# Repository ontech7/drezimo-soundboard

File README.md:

<h1>
  <picture>
    <source media="(prefers-color-scheme: dark)" srcset="assets/logo/drezimo-logo-dark.svg">
    
  </picture>
</h1>

A physical soundboard for [Voicemod](https://www.voicemod.net/): 36 pads, 6 function keys, a rotary encoder and a small OLED display, connected to the PC with a single USB cable.

**Status:** the first unit is built and works: the PCB (v0.2) with its keys, LEDs, display and knob, closed in its 3D-printed enclosure. The desktop app runs on Windows and macOS (Apple Silicon), comes with an installer for each and keeps itself and the board's firmware up to date.

## Hardware

- RP2040-Zero (RP2040, USB-C)
- 6×6 sound pads + 6 function keys, MX switches soldered to the PCB, 7×6 diode matrix
- 42 SK6812MINI-E reverse-mount RGB LEDs, one per key
- 1.3" SH1106 OLED (I²C) and an EC11 encoder with push button
- Custom 2-layer PCB
- 3D-printed enclosure in two parts, a top shell and a bottom, closed by six M3 screws from below
- Powered from USB only

<p align="center">
  
  <br>
  <sub>The bottom of the PCB v0.2 as the fab assembles it: the LEDs and the small parts. The switches, the RP2040-Zero, the LED buffer, the knob and the display are soldered by hand.</sub>
</p>

<table>
  <tr>
    <td width="50%"></td>
    <td width="50%"></td>
  </tr>
  <tr>
    <td align="center"><sub>The top shell: the logo and the function keys' labels are printed flush in white</sub></td>
    <td align="center"><sub>The bottom, from inside: six standoffs for the screws, ribs and posts under the keys, keyholes for an optional stand</sub></td>
  </tr>
</table>

## The app

- **Soundboard:** the board's current page in the window, with Voicemod's pictures and the LEDs' live colours, playable from there too, and the display's live picture. Voicemod's soundboards and voices come as pages of 36 pads; a sound outside the Voicemod licence blinks red with "PRO ONLY" when pressed.
- **Your own pages:** sounds, voices and actions (stop the sounds, mute the microphone, the voice changer, a random voice, hear myself, mute for me, background effects, go to a page, the overlay, the volumes back) in the order you want, with your own names, LED colours and sound volumes, before Voicemod's soundboards on the board.
- **Macros:** one pad playing sounds on tracks along a time line, one after the other or over each other, cut where you want and with their own volume, with voices and switches at their times; How it works walks through the editor with a time line to try.
- **PC overlay:** the page's sounds on top of the other windows when the page changes or the knob is held, on the screen and in the corner you choose.
- **Action wheel:** if you want it, a knob gesture opens a wheel of your shortcuts on the screen, pages, actions or macros around the Drezimo logo, and turning the knob picks one.
- **Updates:** the app updates itself and the board's firmware, and says what is new.
- **Support:** a report to copy, without personal paths, and a hardware test for a board just built.
- In English and Italian.

<p align="center">
  
  <br>
  <sub>The Macro editor: sounds on tracks along a time line, the music fading in and out under the others, voices and switches at their times</sub>
</p>

<table>
  <tr>
    <td width="56%"></td>
    <td width="44%"></td>
  </tr>
  <tr>
    <td align="center"><sub>The page editor</sub></td>
    <td align="center"><sub>The action wheel, picked by turning the knob</sub></td>
  </tr>
</table>

<p align="center">
  
  <br>
  <sub>The PC overlay</sub>
</p>

## Installing the app

Download the Windows installer (`-setup.exe`) from [Releases](https://github.com/ontech7/drezimo-soundboard/releases). It needs Voicemod, free or PRO, on the same PC. The app then starts with Windows, in the notification area, and keeps itself and the board's firmware up to date. The installer is not code-signed: at the first install Windows asks to confirm an unknown publisher (More info → Run anyway).

On a Mac with Apple Silicon, download the disk image (`.dmg`), open it and drag Drezimo Soundboard to Applications. It also needs Voicemod, and keeps itself and the board's firmware up to date; starting with macOS is a switch in its Settings. The app is not signed by Apple: the first time, macOS refuses to open it, then System Settings → Privacy & Security → Open Anyway lets it start (or run `xattr -cr "/Applications/Drezimo Soundboard.app"`).

## How it works

The board talks to a desktop bridge app over USB. The app controls Voicemod through its Control API and reads Voicemod's log to know which sounds are actually playing, so the LEDs and the display match Voicemod's own soundboard. The app draws the display's pictures and the board shows them, so the texts are translated in the app.

## Repository layout

| Path | Contents |
|---|---|
| `hardware/scripts/` | Python scripts that generate the KiCad schematic and PCB, check the design and export review documents and fab files |
| `hardware/pcb/` | KiCad 10 project, generated by the scripts |
| `firmware/` | RP2040-Zero firmware (Arduino core for RP2040, built with `arduino-cli`) |
| `app/` | Bridge app for macOS and Windows (Tauri 2: Rust core, React settings window) |
| `site/` | Landing page with the board in 3D (three.js, Vite) and the latest installer; a Dockerfile serves it with nginx |
| `hardware/lib/` | Project symbol and footprints (RP2040-Zero, MX switch, logo silkscreen) |
| `hardware/enclosure/` | The 3D-printed enclosure, generated from the PCB file and caliper readings (Python, build123d): the generator, its tests and the print files |
| `assets/logo/` | Logo (SVG) and app icon |
| `simulator/dummy-board.html` | 1:1 browser simulator of the board; can connect to Voicemod |
| `tools/` | Voicemod API probe, log watcher and behaviour experiments |
| `docs/` | Design notes and decisions (`project.md`), screenshots |

## Building the hardware files

Requires KiCad 10. On macOS:

```sh
cd hardware/scripts
python3 build_schematic.py
python3 check_design.py
/Applications/KiCad/KiCad.app/Contents/Frameworks/Python.framework/Versions/Current/bin/python3 build_pcb.py
python3 export_docs.py   # schematic PDF, 1:1 fit-check PDFs, 3D renders, DRC report in hardware/docs/
/Applications/KiCad/KiCad.app/Contents/Frameworks/Python.framework/Versions/Current/bin/python3 export_fab.py
```

`build_pcb.py` and `export_fab.py` need KiCad's bundled Python, which provides the `pcbnew` module. Edit the scripts, not the generated KiCad files.

`export_fab.py` writes the JLCPCB package to `hardware/fab/`: the Gerber + drill zip, the assembly BOM with LCSC part numbers and the placement file (CPL). All assembled parts are on the bottom side; the SK6812MINI-E is a JLCPCB "Standard PCBA only" part. The switches, the RP2040-Zero, the SN74AHCT125N, the OLED module and the encoder are hand-soldered.

## Building the enclosure files

Requires [`uv`](https://docs.astral.sh/uv/), which installs Python and build123d on the first run.

```sh
cd hardware/enclosure
uv run python -m drezimo_case shell    # the top shell
uv run python -m drezimo_case bottom   # the bottom
uv run pytest -q
```

Each command writes the part to `hardware/enclosure/print/` as STEP and 3MF, lying as it is printed, with a picture of it cut through. With `--bambu` after the name, and Bambu Studio installed (macOS), it also writes a Bambu Studio project for the P1S with the print settings decided, sliced once as a check. The parts are drawn from the PCB file and from the caliper readings in `drezimo_case/measurements.py`; `docs/project.md` (section 7) says how.

## Building the firmware

Requires [`arduino-cli`](https://arduino.github.io/arduino-cli/) (`brew install arduino-cli` on macOS). The core and library versions are pinned in `firmware/drezimo/sketch.yaml` and downloaded on the first build.

```sh
./firmware/upload.sh          # build, then upload to the connected board
./firmware/build.sh --bundle  # build, then put the firmware into the app
```

The script works with the firmware running (it sends `BOOT` to reach the bootloader) or with the board already in bootloader mode: a blank module, or one plugged in while holding BOOT. It uploads with `picotool`; on macOS, copying the `.uf2` onto the RPI-RP2 drive can hang. It also sets the name the PC shows for the device: **Drezimo Soundboard**.

The app carries the firmware (`app/src-tauri/firmware/drezimo-<version>.uf2` and `.bin`) and updates every board with an older one as soon as it connects, over the USB serial link: nothing shows on the PC. After changing the firmware, raise `FIRMWARE_VERSION` in `firmware/drezimo/drezimo.ino` and run `build.sh --bundle`; the app's build stops while the two versions differ.

## Building the app

Requires [Rust](https://rustup.rs/), Node.js and Yarn 1, plus Tauri's [system prerequisites](https://v2.tauri.app/start/prerequisites/).

```sh
cd app
yarn install
yarn tauri dev     # run with live reload; the app lives in the menu bar / notification area
yarn tauri build   # the Windows installer, or the macOS app (its disk image: see the Release workflow)
cd src-tauri && cargo test
```

The Voicemod client key is built into the app. Request your own at [control-api.voicemod.net](https://control-api.voicemod.net/), then copy `.env.example` to `.env` at the repository root (git ignores it) and set `VOICEMOD_CLIENT_KEY`, or set it in the environment. Without it the app builds and runs, but cannot reach Voicemod.

A build made this way does not update itself: only the published ones do. To publish a version, raise `version` in `app/src-tauri/tauri.conf.json`, bring it to `main` and run **Actions → Release**, which builds both platforms and publishes them together, with what is new in one short line in its **notes** field, if anything: the installed apps show it once they have updated, unless the version has its own news in `app/src/news/changelog.tsx`, shown in a dialog in the app's language. The workflow needs three repository secrets: `VOICEMOD_CLIENT_KEY`, and the updater's private key and password as `TAURI_SIGNING_PRIVATE_KEY` and `TAURI_SIGNING_PRIVATE_KEY_PASSWORD` (made with `yarn tauri signer generate`; the public key is in `tauri.conf.json`).

Close the simulator page before running the app: only one program at a time can hold the board's serial port.

## Tools

```sh
pip install -r requirements.txt
python tools/voicemod_log_bridge.py   # live playback state on ws://localhost:59200
```

Open `simulator/dummy-board.html` in a browser to try the board without hardware.

## License

- Everything but the hardware design (the app, firmware, simulator, tools, `hardware/scripts/`, logo and docs): [MIT](LICENSE).
- Hardware design (`hardware/pcb/`, `hardware/lib/`, `hardware/enclosure/`): [CERN-OHL-P-2.0](hardware/LICENSE).
- Fonts: Silkscreen on the display and Inter in the PC overlay, both under the SIL Open Font License, with their licences in `app/src-tauri/src/display/` and `app/src-tauri/src/overlay/`.
- The firmware image in `app/src-tauri/firmware/` is built from `firmware/` with the Arduino core for RP2040 (LGPL-2.1) and the libraries pinned in `firmware/drezimo/sketch.yaml` (Adafruit NeoPixel, LGPL-3.0; U8g2, BSD-2-Clause).

Voicemod is a trademark of its owner. This project is independent and not affiliated with Voicemod.

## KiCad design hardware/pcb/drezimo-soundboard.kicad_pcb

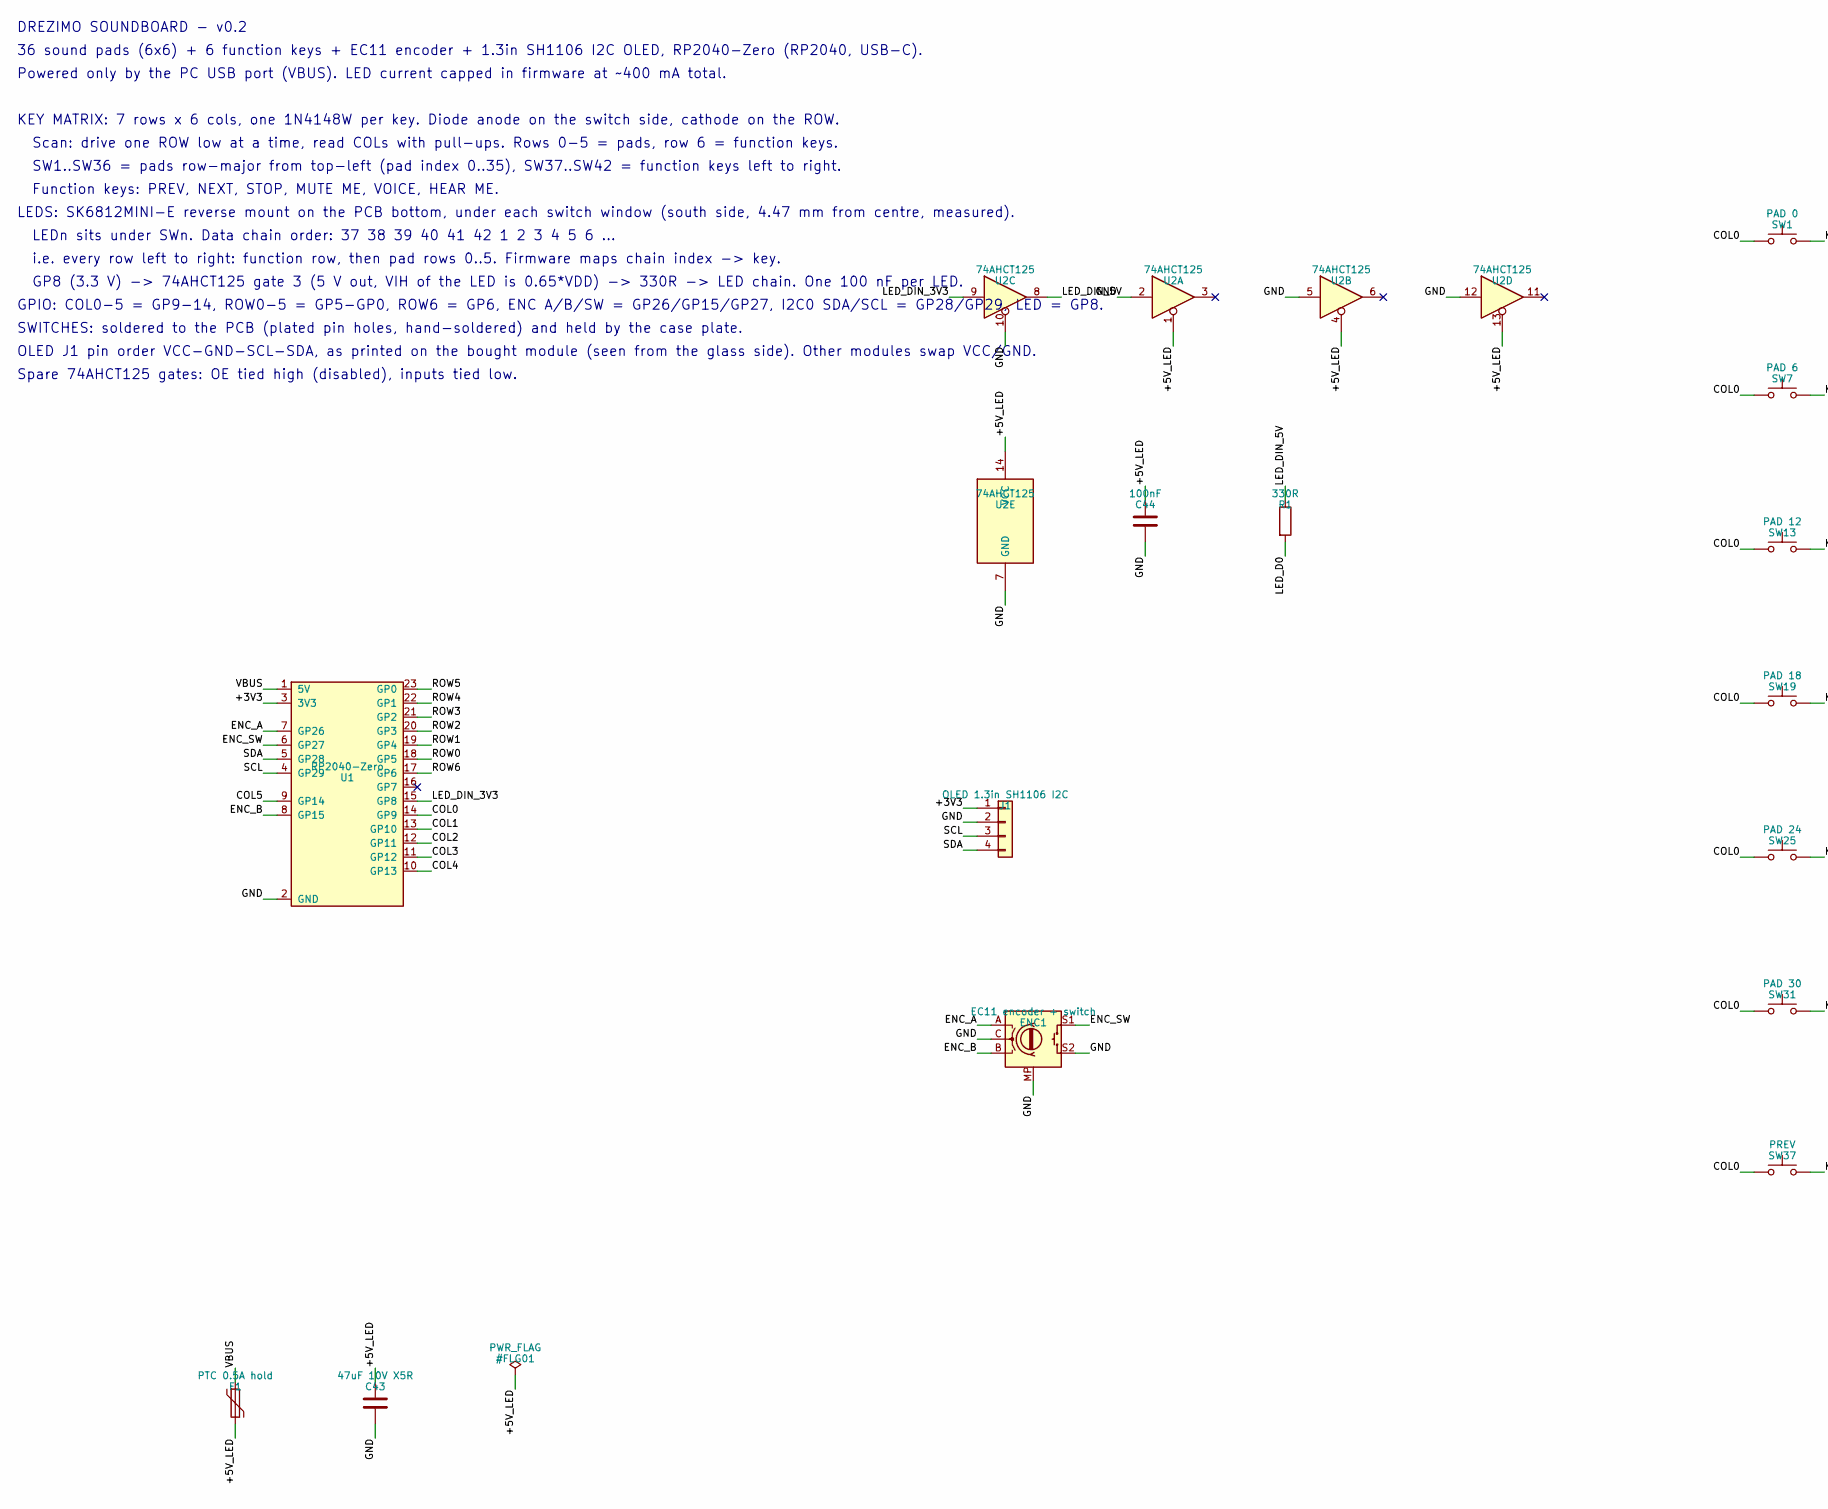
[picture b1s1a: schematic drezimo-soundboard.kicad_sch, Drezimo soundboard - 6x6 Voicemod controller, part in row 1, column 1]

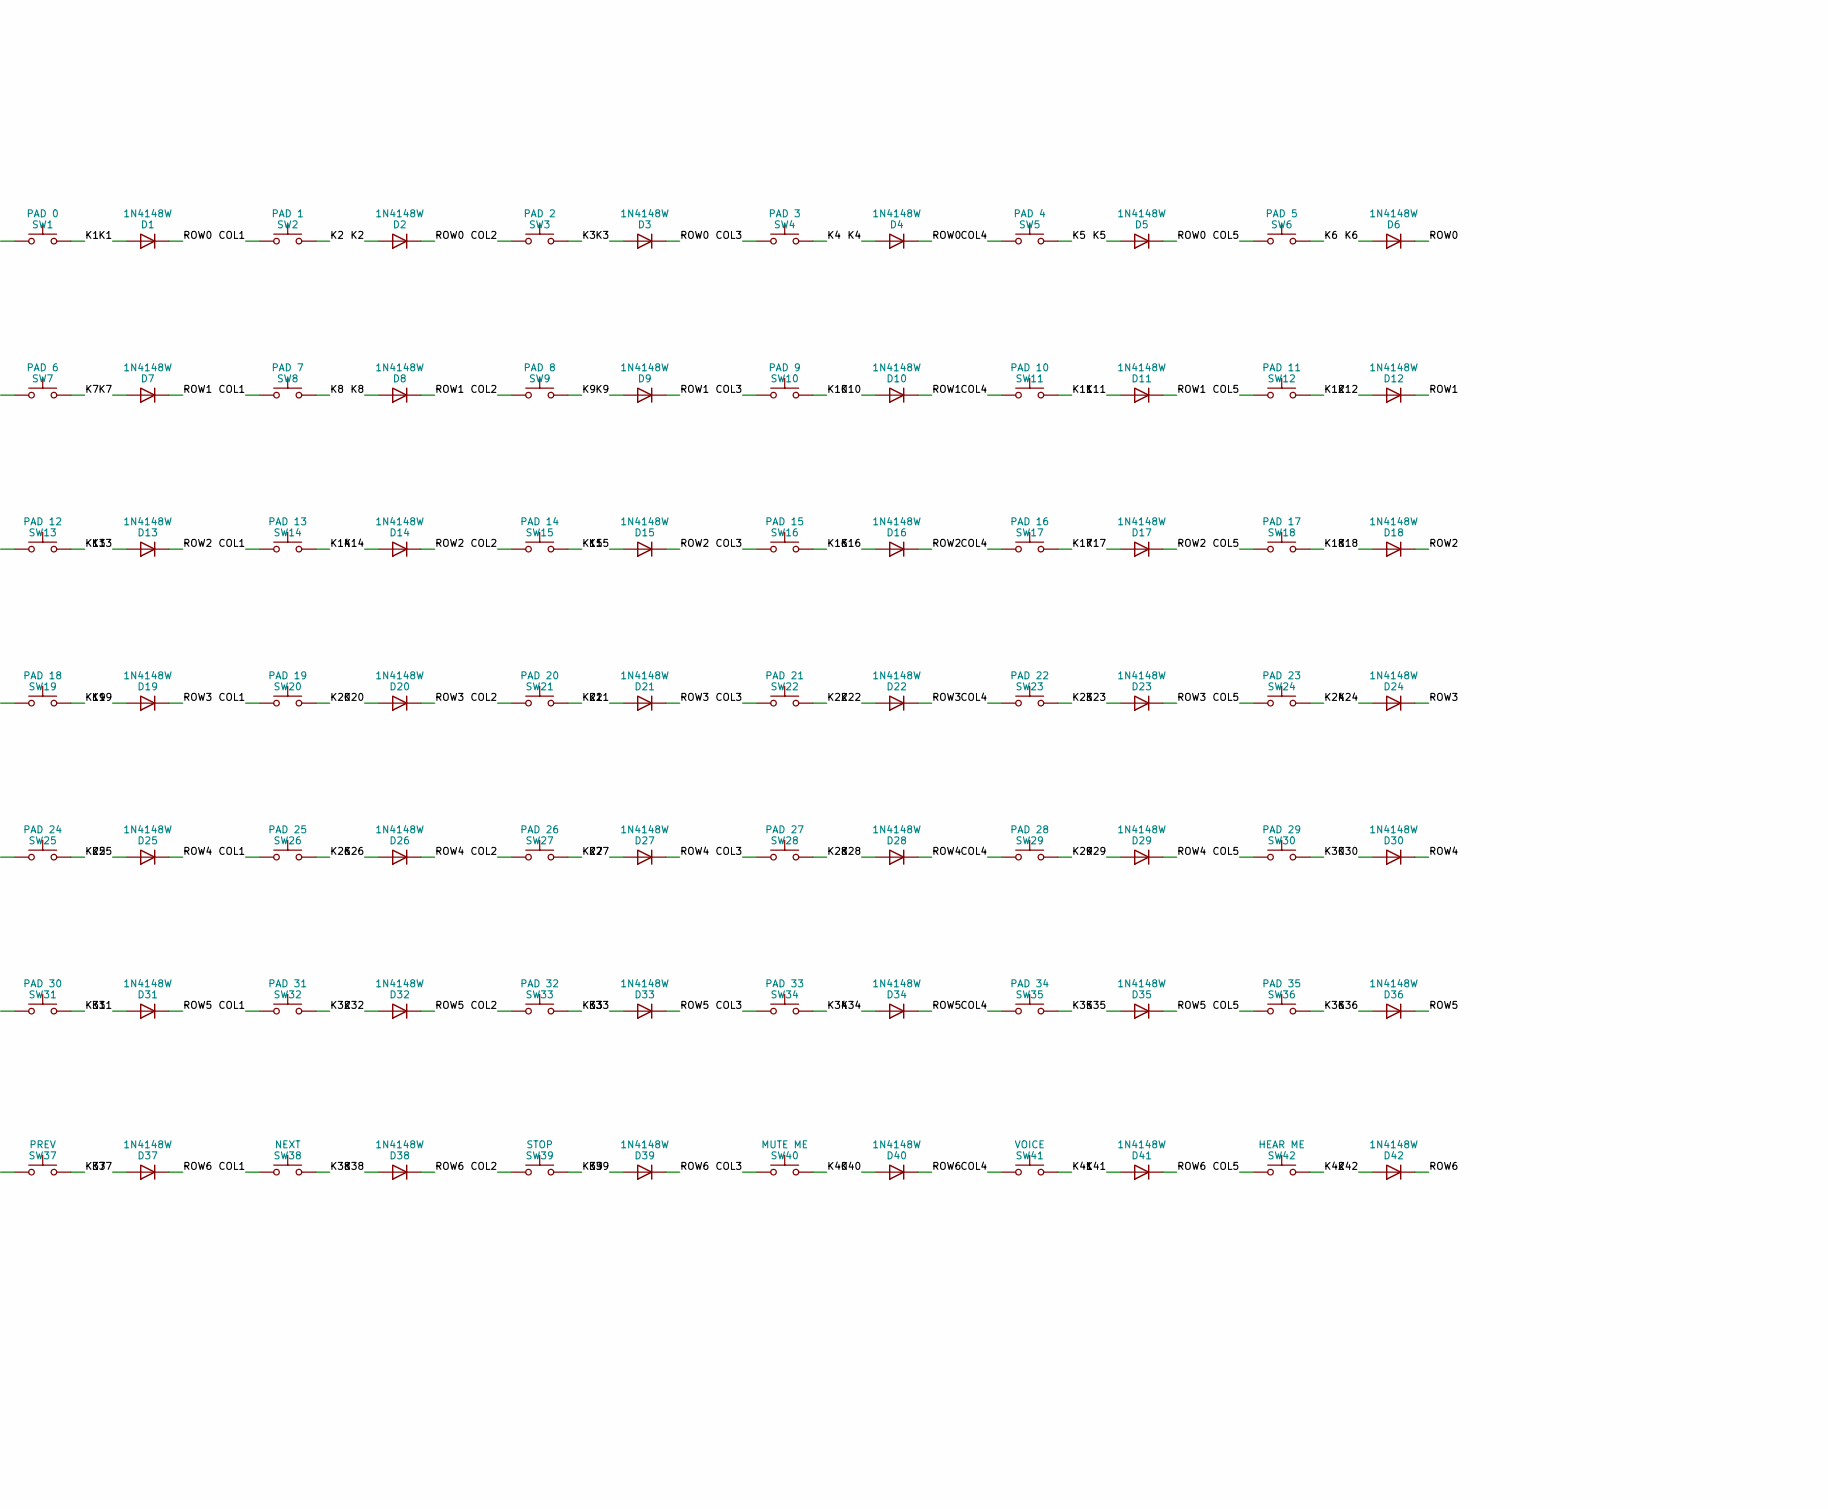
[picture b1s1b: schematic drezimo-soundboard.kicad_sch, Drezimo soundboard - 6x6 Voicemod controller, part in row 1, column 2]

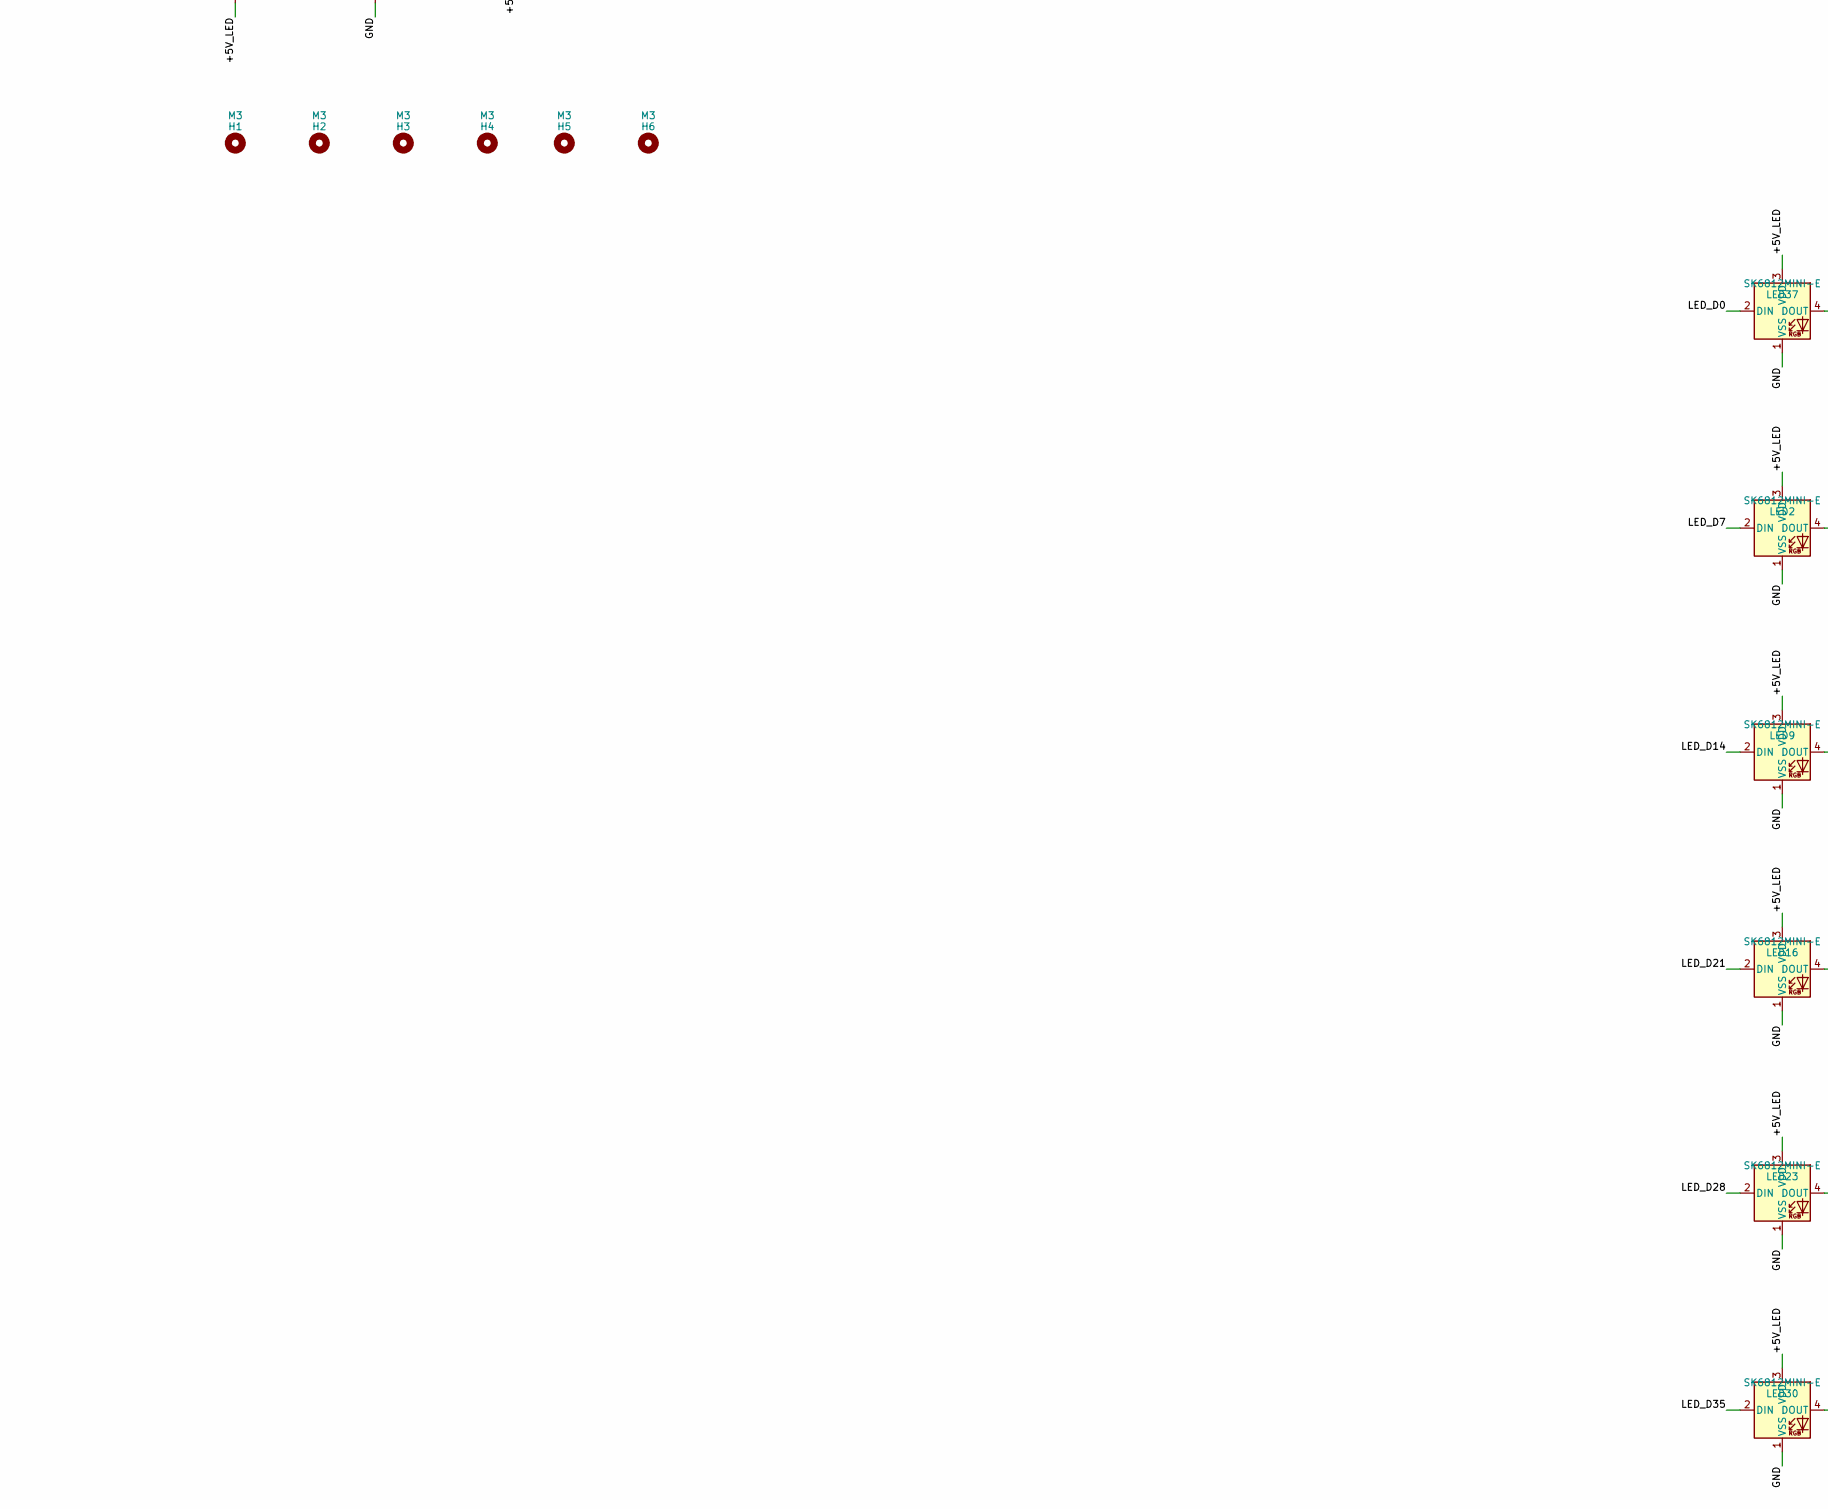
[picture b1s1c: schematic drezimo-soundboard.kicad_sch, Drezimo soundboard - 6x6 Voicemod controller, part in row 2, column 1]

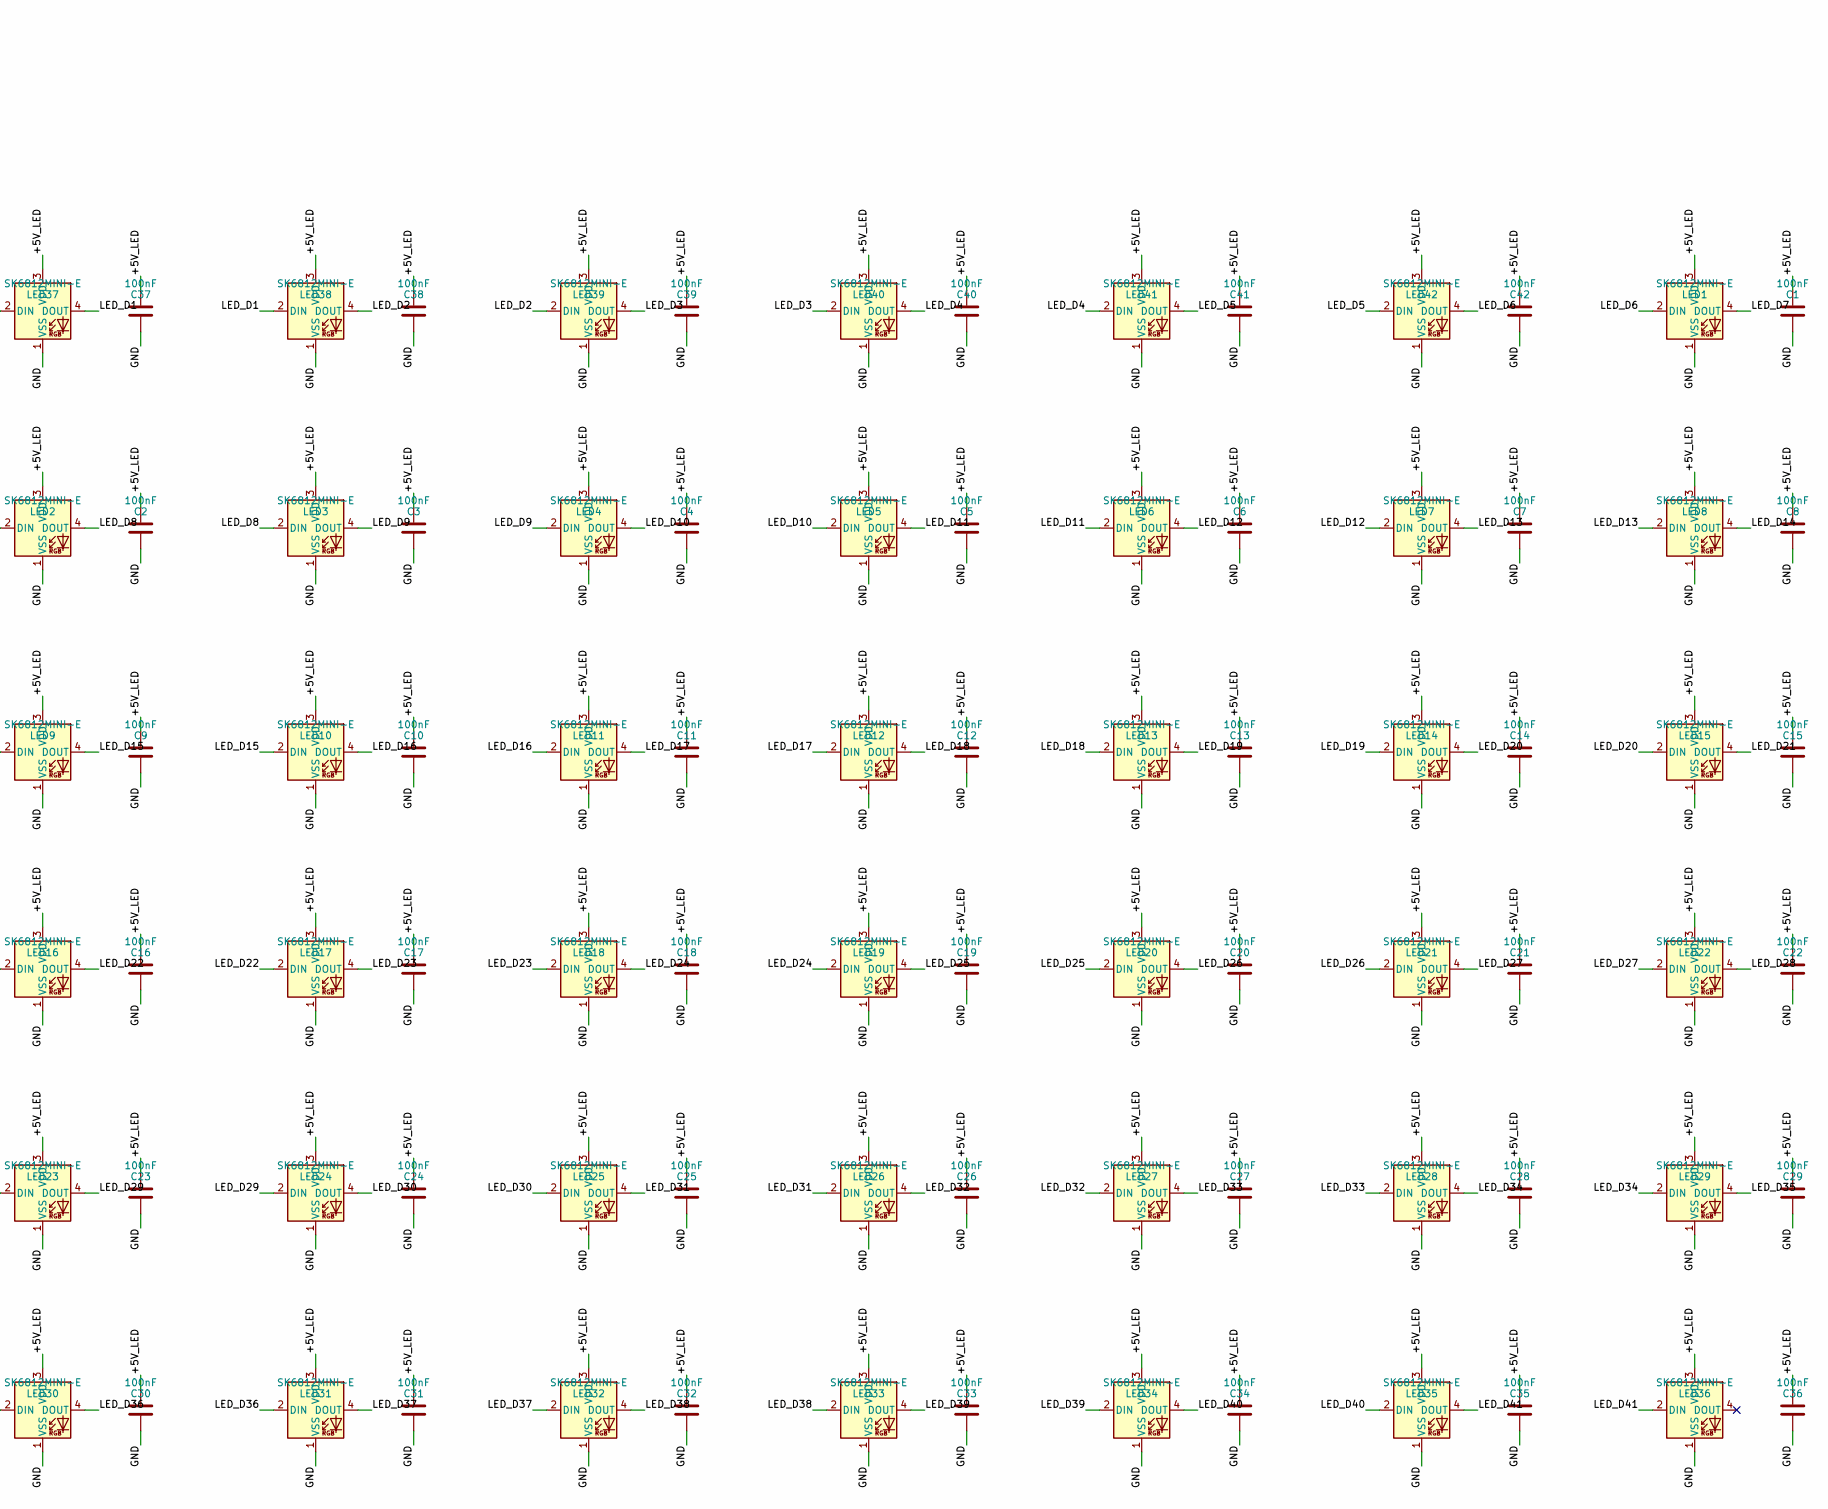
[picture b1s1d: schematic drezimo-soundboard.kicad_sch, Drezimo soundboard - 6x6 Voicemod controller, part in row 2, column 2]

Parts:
C1, C2, C3, C4, C5, C6, C7, C8, C9, C10, C11, C12, C13, C14, C15, C16, C17, C18, C19, C20, C21, C22, C23, C24, C25, C26, C27, C28, C29, C30, C31, C32, C33, C34, C35, C36, C37, C38, C39, C40, C41, C42, C44: 100nF; C_0603_1608Metric; LCSC C14663
C43: 47uF 10V X5R; C_1206_3216Metric; LCSC C96123
D1, D2, D3, D4, D5, D6, D7, D8, D9, D10, D11, D12, D13, D14, D15, D16, D17, D18, D19, D20, D21, D22, D23, D24, D25, D26, D27, D28, D29, D30, D31, D32, D33, D34, D35, D36, D37, D38, D39, D40, D41, D42: 1N4148W; D_SOD-123; LCSC C81598
ENC1: EC11 encoder + switch; RotaryEncoder_Alps_EC11E-Switch_Vertical_H20mm
F1: PTC 0.5A hold; Fuse_1206_3216Metric; LCSC C720075
H1, H2, H3, H4, H5, H6: M3; MountingHole_3.2mm_M3
J1: OLED 1.3in SH1106 I2C; PinHeader_1x04_P2.54mm_Vertical
LED1, LED2, LED3, LED4, LED5, LED6, LED7, LED8, LED9, LED10, LED11, LED12, LED13, LED14, LED15, LED16, LED17, LED18, LED19, LED20, LED21, LED22, LED23, LED24, LED25, LED26, LED27, LED28, LED29, LED30, LED31, LED32, LED33, LED34, LED35, LED36, LED37, LED38, LED39, LED40, LED41, LED42: SK6812MINI-E; LED_SK6812MINI-E_3.2x2.8mm_P1.5mm_ReverseMount; LCSC C5149201
R1: 330R; R_0603_1608Metric; LCSC C23138
SW1: PAD 0; SW_MX_PCB
SW2: PAD 1; SW_MX_PCB
SW3: PAD 2; SW_MX_PCB
SW4: PAD 3; SW_MX_PCB
SW5: PAD 4; SW_MX_PCB
SW6: PAD 5; SW_MX_PCB
SW7: PAD 6; SW_MX_PCB
SW8: PAD 7; SW_MX_PCB
SW9: PAD 8; SW_MX_PCB
SW10: PAD 9; SW_MX_PCB
SW11: PAD 10; SW_MX_PCB
SW12: PAD 11; SW_MX_PCB
SW13: PAD 12; SW_MX_PCB
SW14: PAD 13; SW_MX_PCB
SW15: PAD 14; SW_MX_PCB
SW16: PAD 15; SW_MX_PCB
SW17: PAD 16; SW_MX_PCB
SW18: PAD 17; SW_MX_PCB
SW19: PAD 18; SW_MX_PCB
SW20: PAD 19; SW_MX_PCB
SW21: PAD 20; SW_MX_PCB
SW22: PAD 21; SW_MX_PCB
SW23: PAD 22; SW_MX_PCB
SW24: PAD 23; SW_MX_PCB
SW25: PAD 24; SW_MX_PCB
SW26: PAD 25; SW_MX_PCB
SW27: PAD 26; SW_MX_PCB
SW28: PAD 27; SW_MX_PCB
SW29: PAD 28; SW_MX_PCB
SW30: PAD 29; SW_MX_PCB
SW31: PAD 30; SW_MX_PCB
SW32: PAD 31; SW_MX_PCB
SW33: PAD 32; SW_MX_PCB
SW34: PAD 33; SW_MX_PCB
SW35: PAD 34; SW_MX_PCB
SW36: PAD 35; SW_MX_PCB
SW37: PREV; SW_MX_PCB
SW38: NEXT; SW_MX_PCB
SW39: STOP; SW_MX_PCB
SW40: MUTE ME; SW_MX_PCB
SW41: VOICE; SW_MX_PCB
SW42: HEAR ME; SW_MX_PCB
U1: RP2040-Zero
U2: 74AHCT125; DIP-14_W7.62mm

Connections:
/+3V3: J1.1, U1.3 (3V3)
/+5V_LED: C1.1, C2.1, C3.1, C4.1, C5.1, C6.1, C7.1, C8.1, C9.1, C10.1, C11.1, C12.1, C13.1, C14.1, C15.1, C16.1, C17.1, C18.1, C19.1, C20.1, C21.1, C22.1, C23.1, C24.1, C25.1, C26.1, C27.1, C28.1, C29.1, C30.1, C31.1, C32.1, C33.1, C34.1, C35.1, C36.1, C37.1, C38.1, C39.1, C40.1, C41.1, C42.1, C43.1, C44.1, F1.2, LED1.3 (VDD), LED2.3 (VDD), LED3.3 (VDD), LED4.3 (VDD), LED5.3 (VDD), LED6.3 (VDD), LED7.3 (VDD), LED8.3 (VDD), LED9.3 (VDD), LED10.3 (VDD), LED11.3 (VDD), LED12.3 (VDD), LED13.3 (VDD), LED14.3 (VDD), LED15.3 (VDD), LED16.3 (VDD), LED17.3 (VDD), LED18.3 (VDD), LED19.3 (VDD), LED20.3 (VDD), LED21.3 (VDD), LED22.3 (VDD), LED23.3 (VDD), LED24.3 (VDD), LED25.3 (VDD), LED26.3 (VDD), LED27.3 (VDD), LED28.3 (VDD), LED29.3 (VDD), LED30.3 (VDD), LED31.3 (VDD), LED32.3 (VDD), LED33.3 (VDD), LED34.3 (VDD), LED35.3 (VDD), LED36.3 (VDD), LED37.3 (VDD), LED38.3 (VDD), LED39.3 (VDD), LED40.3 (VDD), LED41.3 (VDD), LED42.3 (VDD), U2.1, U2.4, U2.13, U2.14 (VCC)
/COL0: SW1.1, SW7.1, SW13.1, SW19.1, SW25.1, SW31.1, SW37.1, U1.14 (GP9)
/COL1: SW2.1, SW8.1, SW14.1, SW20.1, SW26.1, SW32.1, SW38.1, U1.13 (GP10)
/COL2: SW3.1, SW9.1, SW15.1, SW21.1, SW27.1, SW33.1, SW39.1, U1.12 (GP11)
/COL3: SW4.1, SW10.1, SW16.1, SW22.1, SW28.1, SW34.1, SW40.1, U1.11 (GP12)
/COL4: SW5.1, SW11.1, SW17.1, SW23.1, SW29.1, SW35.1, SW41.1, U1.10 (GP13)
/COL5: SW6.1, SW12.1, SW18.1, SW24.1, SW30.1, SW36.1, SW42.1, U1.9 (GP14)
/ENC_A: ENC1.A, U1.7 (GP26)
/ENC_B: ENC1.B, U1.8 (GP15)
/ENC_SW: ENC1.S1, U1.6 (GP27)
/GND: C1.2, C2.2, C3.2, C4.2, C5.2, C6.2, C7.2, C8.2, C9.2, C10.2, C11.2, C12.2, C13.2, C14.2, C15.2, C16.2, C17.2, C18.2, C19.2, C20.2, C21.2, C22.2, C23.2, C24.2, C25.2, C26.2, C27.2, C28.2, C29.2, C30.2, C31.2, C32.2, C33.2, C34.2, C35.2, C36.2, C37.2, C38.2, C39.2, C40.2, C41.2, C42.2, C43.2, C44.2, ENC1.C, ENC1.MP, ENC1.S2, J1.2, LED1.1 (VSS), LED2.1 (VSS), LED3.1 (VSS), LED4.1 (VSS), LED5.1 (VSS), LED6.1 (VSS), LED7.1 (VSS), LED8.1 (VSS), LED9.1 (VSS), LED10.1 (VSS), LED11.1 (VSS), LED12.1 (VSS), LED13.1 (VSS), LED14.1 (VSS), LED15.1 (VSS), LED16.1 (VSS), LED17.1 (VSS), LED18.1 (VSS), LED19.1 (VSS), LED20.1 (VSS), LED21.1 (VSS), LED22.1 (VSS), LED23.1 (VSS), LED24.1 (VSS), LED25.1 (VSS), LED26.1 (VSS), LED27.1 (VSS), LED28.1 (VSS), LED29.1 (VSS), LED30.1 (VSS), LED31.1 (VSS), LED32.1 (VSS), LED33.1 (VSS), LED34.1 (VSS), LED35.1 (VSS), LED36.1 (VSS), LED37.1 (VSS), LED38.1 (VSS), LED39.1 (VSS), LED40.1 (VSS), LED41.1 (VSS), LED42.1 (VSS), U1.2 (GND), U2.2, U2.5, U2.7 (GND), U2.10, U2.12
/K1: D1.2 (A), SW1.2
/K2: D2.2 (A), SW2.2
/K3: D3.2 (A), SW3.2
/K4: D4.2 (A), SW4.2
/K5: D5.2 (A), SW5.2
/K6: D6.2 (A), SW6.2
/K7: D7.2 (A), SW7.2
/K8: D8.2 (A), SW8.2
/K9: D9.2 (A), SW9.2
/K10: D10.2 (A), SW10.2
/K11: D11.2 (A), SW11.2
/K12: D12.2 (A), SW12.2
/K13: D13.2 (A), SW13.2
/K14: D14.2 (A), SW14.2
/K15: D15.2 (A), SW15.2
/K16: D16.2 (A), SW16.2
/K17: D17.2 (A), SW17.2
/K18: D18.2 (A), SW18.2
/K19: D19.2 (A), SW19.2
/K20: D20.2 (A), SW20.2
/K21: D21.2 (A), SW21.2
/K22: D22.2 (A), SW22.2
/K23: D23.2 (A), SW23.2
/K24: D24.2 (A), SW24.2
/K25: D25.2 (A), SW25.2
/K26: D26.2 (A), SW26.2
/K27: D27.2 (A), SW27.2
/K28: D28.2 (A), SW28.2
/K29: D29.2 (A), SW29.2
/K30: D30.2 (A), SW30.2
/K31: D31.2 (A), SW31.2
/K32: D32.2 (A), SW32.2
/K33: D33.2 (A), SW33.2
/K34: D34.2 (A), SW34.2
/K35: D35.2 (A), SW35.2
/K36: D36.2 (A), SW36.2
/K37: D37.2 (A), SW37.2
/K38: D38.2 (A), SW38.2
/K39: D39.2 (A), SW39.2
/K40: D40.2 (A), SW40.2
/K41: D41.2 (A), SW41.2
/K42: D42.2 (A), SW42.2
/LED_D0: LED37.2 (DIN), R1.2
/LED_D1: LED37.4 (DOUT), LED38.2 (DIN)
/LED_D2: LED38.4 (DOUT), LED39.2 (DIN)
/LED_D3: LED39.4 (DOUT), LED40.2 (DIN)
/LED_D4: LED40.4 (DOUT), LED41.2 (DIN)
/LED_D5: LED41.4 (DOUT), LED42.2 (DIN)
/LED_D6: LED1.2 (DIN), LED42.4 (DOUT)
/LED_D7: LED1.4 (DOUT), LED2.2 (DIN)
/LED_D8: LED2.4 (DOUT), LED3.2 (DIN)
/LED_D9: LED3.4 (DOUT), LED4.2 (DIN)
/LED_D10: LED4.4 (DOUT), LED5.2 (DIN)
/LED_D11: LED5.4 (DOUT), LED6.2 (DIN)
/LED_D12: LED6.4 (DOUT), LED7.2 (DIN)
/LED_D13: LED7.4 (DOUT), LED8.2 (DIN)
/LED_D14: LED8.4 (DOUT), LED9.2 (DIN)
/LED_D15: LED9.4 (DOUT), LED10.2 (DIN)
/LED_D16: LED10.4 (DOUT), LED11.2 (DIN)
/LED_D17: LED11.4 (DOUT), LED12.2 (DIN)
/LED_D18: LED12.4 (DOUT), LED13.2 (DIN)
/LED_D19: LED13.4 (DOUT), LED14.2 (DIN)
/LED_D20: LED14.4 (DOUT), LED15.2 (DIN)
/LED_D21: LED15.4 (DOUT), LED16.2 (DIN)
/LED_D22: LED16.4 (DOUT), LED17.2 (DIN)
/LED_D23: LED17.4 (DOUT), LED18.2 (DIN)
/LED_D24: LED18.4 (DOUT), LED19.2 (DIN)
/LED_D25: LED19.4 (DOUT), LED20.2 (DIN)
/LED_D26: LED20.4 (DOUT), LED21.2 (DIN)
/LED_D27: LED21.4 (DOUT), LED22.2 (DIN)
/LED_D28: LED22.4 (DOUT), LED23.2 (DIN)
/LED_D29: LED23.4 (DOUT), LED24.2 (DIN)
/LED_D30: LED24.4 (DOUT), LED25.2 (DIN)
/LED_D31: LED25.4 (DOUT), LED26.2 (DIN)
/LED_D32: LED26.4 (DOUT), LED27.2 (DIN)
/LED_D33: LED27.4 (DOUT), LED28.2 (DIN)
/LED_D34: LED28.4 (DOUT), LED29.2 (DIN)
/LED_D35: LED29.4 (DOUT), LED30.2 (DIN)
/LED_D36: LED30.4 (DOUT), LED31.2 (DIN)
/LED_D37: LED31.4 (DOUT), LED32.2 (DIN)
/LED_D38: LED32.4 (DOUT), LED33.2 (DIN)
/LED_D39: LED33.4 (DOUT), LED34.2 (DIN)
/LED_D40: LED34.4 (DOUT), LED35.2 (DIN)
/LED_D41: LED35.4 (DOUT), LED36.2 (DIN)
/LED_DIN_3V3: U1.15 (GP8), U2.9
/LED_DIN_5V: R1.1, U2.8
/ROW0: D1.1 (K), D2.1 (K), D3.1 (K), D4.1 (K), D5.1 (K), D6.1 (K), U1.18 (GP5)
/ROW1: D7.1 (K), D8.1 (K), D9.1 (K), D10.1 (K), D11.1 (K), D12.1 (K), U1.19 (GP4)
/ROW2: D13.1 (K), D14.1 (K), D15.1 (K), D16.1 (K), D17.1 (K), D18.1 (K), U1.20 (GP3)
/ROW3: D19.1 (K), D20.1 (K), D21.1 (K), D22.1 (K), D23.1 (K), D24.1 (K), U1.21 (GP2)
/ROW4: D25.1 (K), D26.1 (K), D27.1 (K), D28.1 (K), D29.1 (K), D30.1 (K), U1.22 (GP1)
/ROW5: D31.1 (K), D32.1 (K), D33.1 (K), D34.1 (K), D35.1 (K), D36.1 (K), U1.23 (GP0)
/ROW6: D37.1 (K), D38.1 (K), D39.1 (K), D40.1 (K), D41.1 (K), D42.1 (K), U1.17 (GP6)
/SCL: J1.3, U1.4 (GP29)
/SDA: J1.4, U1.5 (GP28)
/VBUS: F1.1, U1.1 (5V)

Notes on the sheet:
DREZIMO SOUNDBOARD - v0.2
36 sound pads (6x6) + 6 function keys + EC11 encoder + 1.3in SH1106 I2C OLED, RP2040-Zero (RP2040, USB-C).
Powered only by the PC USB port (VBUS). LED current capped in firmware at ~400 mA total.
KEY MATRIX: 7 rows x 6 cols, one 1N4148W per key. Diode anode on the switch side, cathode on the ROW.
Scan: drive one ROW low at a time, read COLs with pull-ups. Rows 0-5 = pads, row 6 = function keys.
SW1..SW36 = pads row-major from top-left (pad index 0..35), SW37..SW42 = function keys left to right.
Function keys: PREV, NEXT, STOP, MUTE ME, VOICE, HEAR ME.
LEDS: SK6812MINI-E reverse mount on the PCB bottom, under each switch window (south side, 4.47 mm from centre, measured).
LEDn sits under SWn. Data chain order: 37 38 39 40 41 42 1 2 3 4 5 6 ...
i.e. every row left to right: function row, then pad rows 0..5. Firmware maps chain index -> key.
GP8 (3.3 V) -> 74AHCT125 gate 3 (5 V out, VIH of the LED is 0.65*VDD) -> 330R -> LED chain. One 100 nF per LED.
GPIO: COL0-5 = GP9-14, ROW0-5 = GP5-GP0, ROW6 = GP6, ENC A/B/SW = GP26/GP15/GP27, I2C0 SDA/SCL = GP28/GP29, LED = GP8.
SWITCHES: soldered to the PCB (plated pin holes, hand-soldered) and held by the case plate.
OLED J1 pin order VCC-GND-SCL-SDA, as printed on the bought module (seen from the glass side). Other modules swap VCC/GND.
Spare 74AHCT125 gates: OE tied high (disabled), inputs tied low.

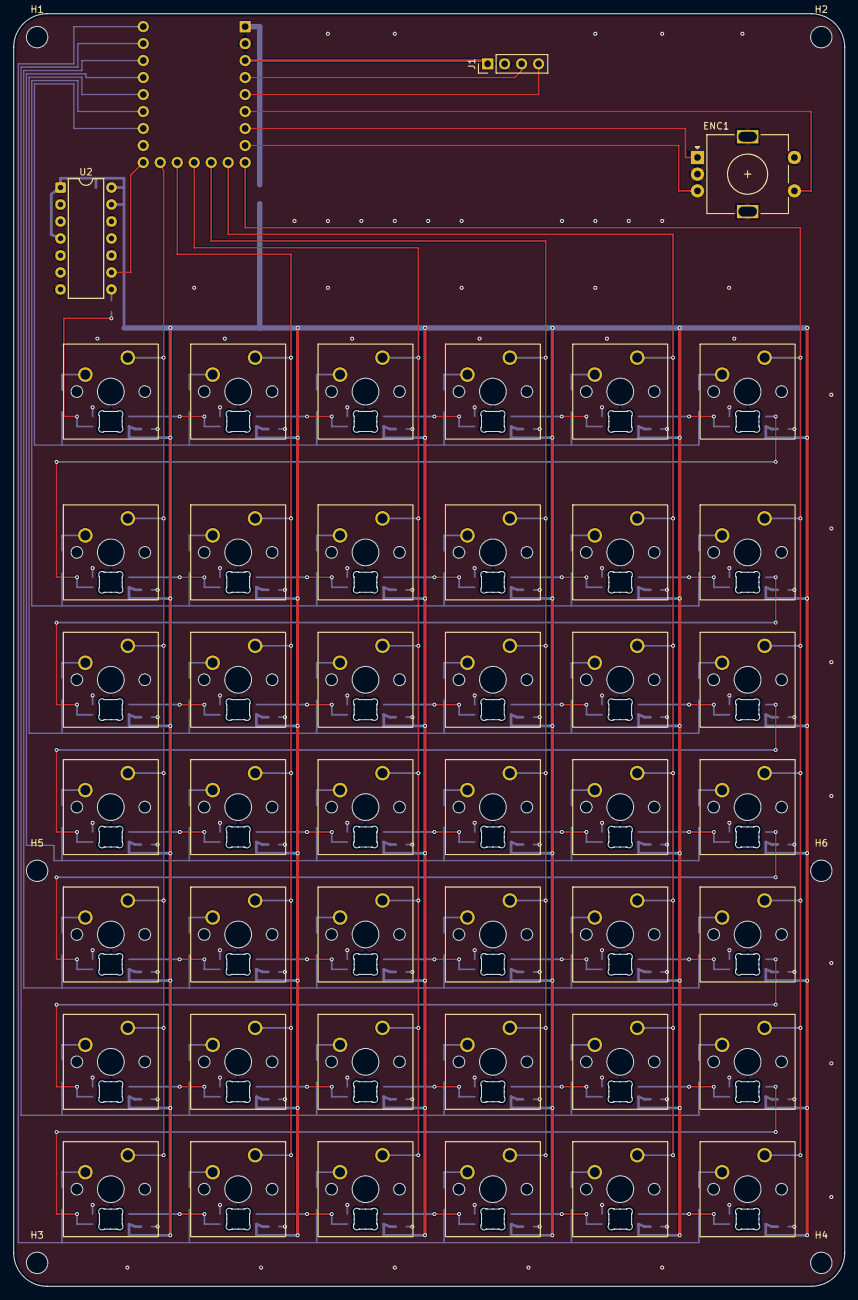
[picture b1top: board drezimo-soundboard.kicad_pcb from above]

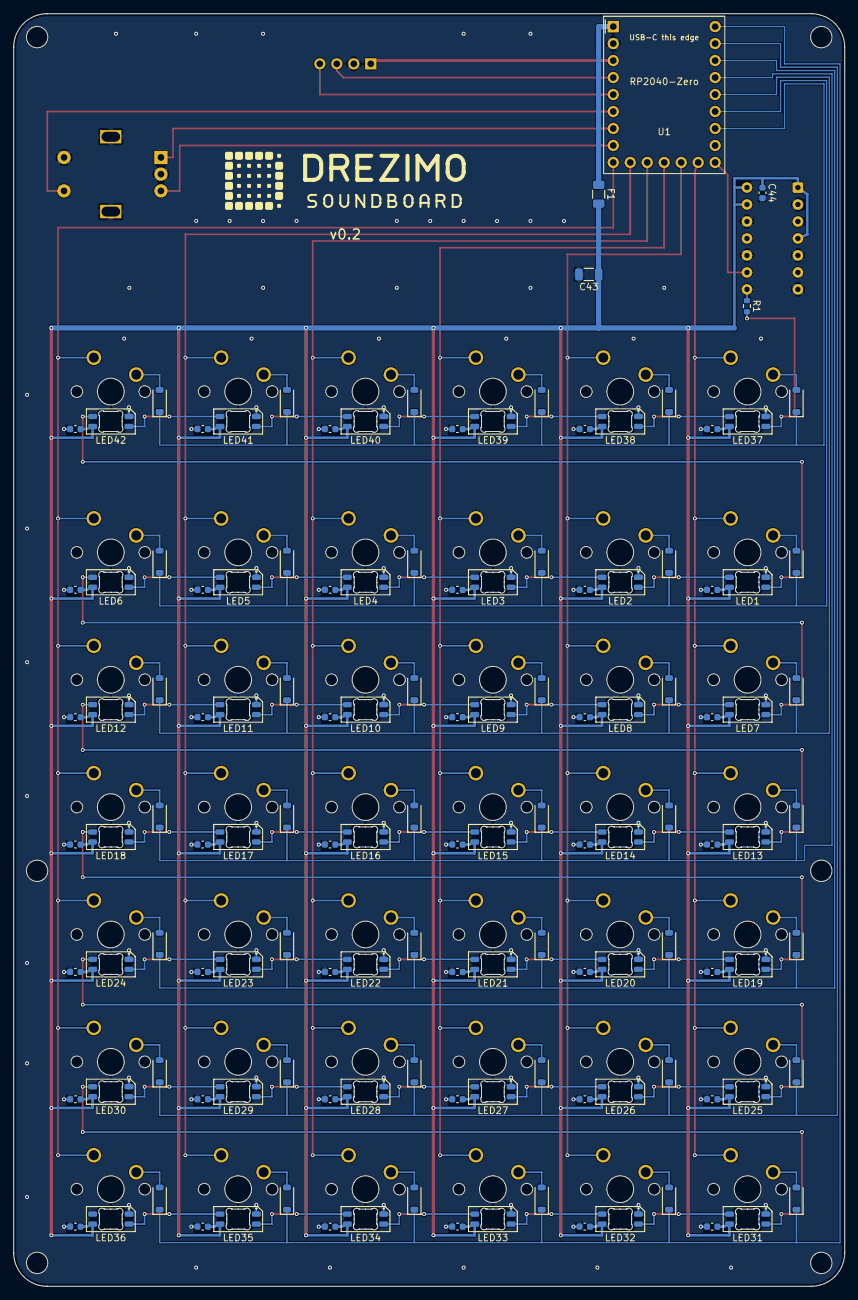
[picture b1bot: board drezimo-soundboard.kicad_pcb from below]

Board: 2 copper layers, 124.3 x 190.3 mm, 183 parts (132 on the bottom side), 108 nets.

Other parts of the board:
LOGO1: Drezimo_Logo

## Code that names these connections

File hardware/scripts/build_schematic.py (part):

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        "  LEDn sits under SWn. Data chain order: " + " ".join(f"{k}" for k in CHAIN_ORDER[:12]) + " ...",
        "  i.e. every row left to right: function row, then pad rows 0..5. Firmware maps chain index -> key.",
        "  GP8 (3.3 V) -> 74AHCT125 gate 3 (5 V out, VIH of the LED is 0.65*VDD) -> 330R -> LED chain. One 100 nF per LED.",
        "GPIO: COL0-5 = GP9-14, ROW0-5 = GP5-GP0, ROW6 = GP6, ENC A/B/SW = GP26/GP15/GP27, I2C0 SDA/SCL = GP28/GP29, LED = GP8.",
        "SWITCHES: soldered to the PCB (plated pin holes, hand-soldered) and held by the case plate.",
        "OLED J1 pin order VCC-GND-SCL-SDA, as printed on the modules used (seen from the glass side). Other modules swap VCC/GND.",
        "Spare 74AHCT125 gates: OE tied high (disabled), inputs tied low.",
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    for pin, net in ((1, "+3V3"), (2, "GND"), (3, "SCL"), (4, "SDA")):
        j1.net(pin, net)
    enc = sch.place("Device", "RotaryEncoder_Switch_MP", "ENC1", "EC11 encoder + switch", "Rotary_Encoder:RotaryEncoder_Alps_EC11E-Switch_Vertical_H20mm", 205, 205)
    for pin, net in (("A", "ENC_A"), ("B", "ENC_B"), ("C", "GND"), ("S1", "ENC_SW"), ("S2", "GND"), ("MP", "GND")):
        enc.net(pin, net)

    # --- Key matrix
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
